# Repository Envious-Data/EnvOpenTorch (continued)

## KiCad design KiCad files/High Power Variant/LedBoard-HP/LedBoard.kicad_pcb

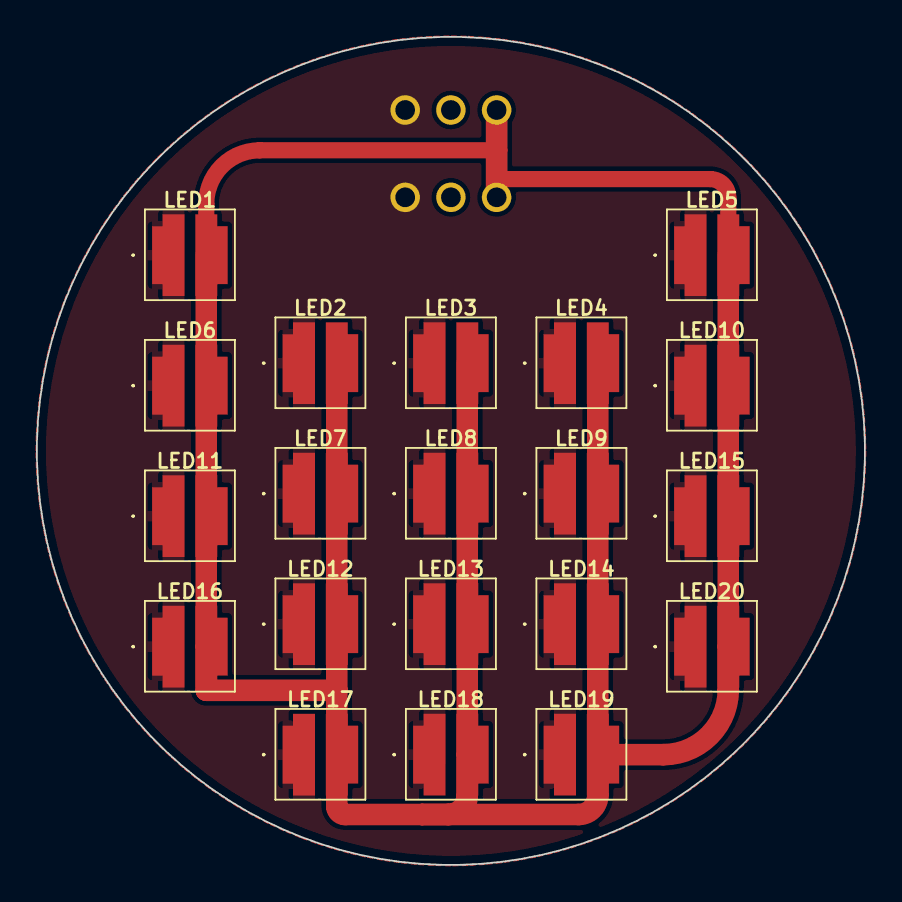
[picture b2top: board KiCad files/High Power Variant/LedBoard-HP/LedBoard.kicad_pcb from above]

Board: 2 copper layers, 46.0 x 46.0 mm, 21 parts (1 on the bottom side), 2 nets.

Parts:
J4: 7-5530843-7; 755308437
LED1, LED2, LED3, LED4, LED5, LED6, LED7, LED8, LED9, LED10, LED11, LED12, LED13, LED14, LED15, LED16, LED17, LED18, LED19, LED20: L1505790500600000

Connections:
GND: J4.5, J4.6, LED1.1 (K_1), LED1.3 (K_2), LED2.1 (K_1), LED2.3 (K_2), LED3.1 (K_1), LED3.3 (K_2), LED4.1 (K_1), LED4.3 (K_2), LED5.1 (K_1), LED5.3 (K_2), LED6.1 (K_1), LED6.3 (K_2), LED7.1 (K_1), LED7.3 (K_2), LED8.1 (K_1), LED8.3 (K_2), LED9.1 (K_1), LED9.3 (K_2), LED10.1 (K_1), LED10.3 (K_2), LED11.1 (K_1), LED11.3 (K_2), LED12.1 (K_1), LED12.3 (K_2), LED13.1 (K_1), LED13.3 (K_2), LED14.1 (K_1), LED14.3 (K_2), LED15.1 (K_1), LED15.3 (K_2), LED16.1 (K_1), LED16.3 (K_2), LED17.1 (K_1), LED17.3 (K_2), LED18.1 (K_1), LED18.3 (K_2), LED19.1 (K_1), LED19.3 (K_2), LED20.1 (K_1), LED20.3 (K_2)
VCC: J4.1, J4.2, LED1.2 (A_1), LED1.4 (A_2), LED2.2 (A_1), LED2.4 (A_2), LED3.2 (A_1), LED3.4 (A_2), LED4.2 (A_1), LED4.4 (A_2), LED5.2 (A_1), LED5.4 (A_2), LED6.2 (A_1), LED6.4 (A_2), LED7.2 (A_1), LED7.4 (A_2), LED8.2 (A_1), LED8.4 (A_2), LED9.2 (A_1), LED9.4 (A_2), LED10.2 (A_1), LED10.4 (A_2), LED11.2 (A_1), LED11.4 (A_2), LED12.2 (A_1), LED12.4 (A_2), LED13.2 (A_1), LED13.4 (A_2), LED14.2 (A_1), LED14.4 (A_2), LED15.2 (A_1), LED15.4 (A_2), LED16.2 (A_1), LED16.4 (A_2), LED17.2 (A_1), LED17.4 (A_2), LED18.2 (A_1), LED18.4 (A_2), LED19.2 (A_1), LED19.4 (A_2), LED20.2 (A_1), LED20.4 (A_2)

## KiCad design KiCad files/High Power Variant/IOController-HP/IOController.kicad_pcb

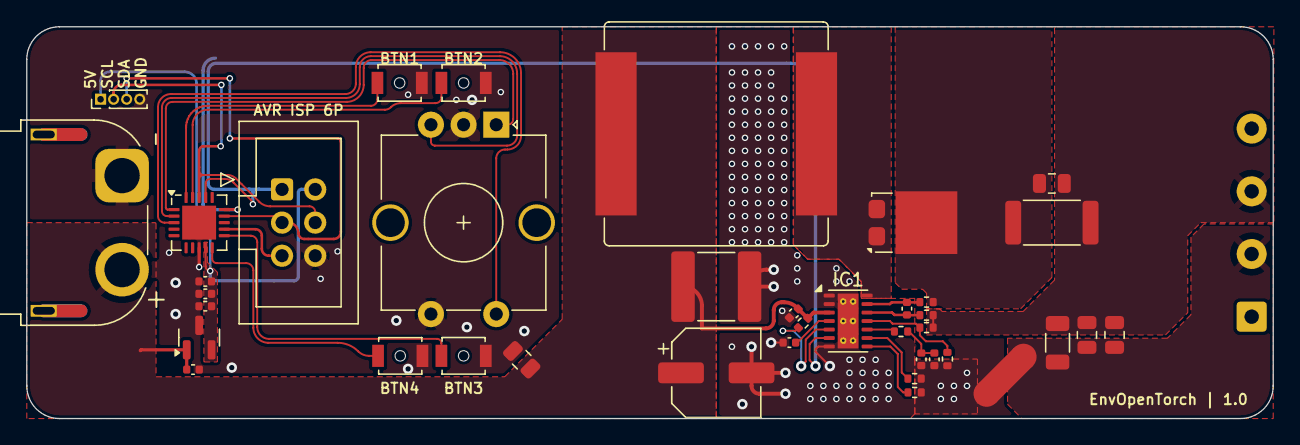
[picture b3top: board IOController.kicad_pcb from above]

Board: 2 copper layers, 95.4 x 30.0 mm, 40 parts (0 on the bottom side), 27 nets.

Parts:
C1: 0401 1uF 35V; C_0402_1005Metric
C2: 0401 2.2uF 6.3V; C_0402_1005Metric
C3: 0401 1uF 6.3V; C_0402_1005Metric
C4: 0401 10uF 6.3V; C_0402_1005Metric
C5: 50V 0.1uF 0805; C_0805_2012Metric
C7: 50V 68uF; CP_Elec_6.3x3
C8: 50V 22uF 2220; C_2220_5750Metric
C12, C13: 25V 1uF 0402; C_0402_1005Metric
C14: 16V 0.1uF 0402; C_0402_1005Metric
C15, C16: 10V 10nF 0402; C_0402_1005Metric
C17: Csense 50V 30uF 0805; C_0805_2012Metric
C18: 100V 0.1uF 0805; C_0805_2012Metric
C19: 100V 1uF 0805; C_0805_2012Metric
C20: 100V 2.2uF 1205; C_1206_3216Metric
D1: FSV12100V; TO-277A
IC1: TPS923654DMTR; VSON-14-1EP_3x4.45mm_P0.65mm_EP1.6x4.2mm_ThermalVias
J1: AVR-ISP-6; IDC-Header_2x03_P2.54mm_Vertical
J2: XT60 Horizontal Socket; AMASS_XT60PW-F_1x02_P7.20mm_Horizontal
J3: Conn_01x04; PinHeader_1x04_P1.00mm_Vertical
J101: Conn_01x04; SolderWire-0.5sqmm_1x04_P4.8mm_D0.9mm_OD2.3mm
L1: SRP1770TA-220M; L_Bourns_SRP1770TA_16.9x16.9mm
NT1: NetTie; NetTie-2_SMD_Pad2.0mm
R5: 10K 0402; R_0402_1005Metric
R6: Rfset 160K 0402; R_0402_1005Metric
R7: Rtemp 57K6 0402; R_0402_1005Metric
R8: Rcomp 825ohm 0402; R_0402_1005Metric
R9: 2512 33mR; R_2512_6332Metric
R10: Rovp1 500K 0402; R_0402_1005Metric
R11: Rovp2 10K 0402; R_0402_1005Metric
R12, R13: 0Ω 0402; R_0402_1005Metric
SW1: EC12; RotaryEncoder_Alps_EC12E-Switch_Vertical_H20mm_CircularMoun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
SW101, SW102, SW103, SW104: B3U; SW_SPST_B3U-1000P-B
U1: AP7384-50SA; SOT-23
U2: ATtiny1634-M; QFN-20-1EP_4x4mm_P0.5mm_EP2.6x2.6mm

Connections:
+5V: C2.1, C3.1, C4.1, J1.2 (VCC), J3.1, U1.2 (VO), U2.9 (VCC)
/LED Driver/CSN: C14.2, IC1.13 (CSN), R12.1
/LED Driver/CSP: C14.1, IC1.12 (CSP), R13.1
/MCU/PC3: J1.5 (~RST), U2.12 (~RESET/PC3)
BTN1: SW101.1, U2.20 (PA7)
BTN2: SW102.1, U2.19 (PB0)
BTN3: SW103.1, U2.11 (XTAL2/PC4)
BTN4: SW104.1, U2.10 (XTAL1/PC5)
BTN5: SW1.S1, U2.3 (PA4)
GND: C1.2, C2.2, C3.2, C4.2, C5.2, C7.2, C8.2, C12.2, C13.1, C15.2, C16.2, IC1.1 (PGND), IC1.2 (AGND), IC1.7 (FAULT), IC1.15 (EP), J1.6 (GND), J2.1, J3.4, NT1.1, R6.2, R7.2, R11.1, SW1.C, SW1.S2, SW101.2, SW102.2, SW103.2, SW104.2, U1.3 (GND), U2.8 (GND), U2.21 (GND)
LED V+: C17.2, C18.1, C19.1, C20.1, J101.3, R9.2, R10.2, R13.2
LED_PWM_5V: IC1.6 (EN/PWM), J1.1 (MISO), U2.17 (PB2)
LED_V-: C18.2, C19.2, C20.2, J101.2, NT1.2
unnamed: C15.1, C16.1, R8.2
unnamed: C17.1, D1.3 (K), R9.1, R12.2
unnamed: IC1.5 (ADIM/HD), R5.2
unnamed: IC1.10 (COMP), R8.1
unnamed: IC1.9 (FSET), R6.1
unnamed: D1.1 (A), D1.2 (A), IC1.14 (SW), L1.2
unnamed: IC1.8 (TEMP), R7.1
unnamed: IC1.11 (UVP), R10.1, R11.2
unnamed: C13.2, IC1.4 (VCC)
ROT_A: SW1.A, U2.1 (PA6)
ROT_B: SW1.B, U2.2 (PA5)
SCL: J1.3 (SCK), J3.3, U2.14 (PC1)
SDA: J1.4 (MOSI), J3.2, U2.18 (PB1)
VCC: C1.1, C5.1, C7.1, C8.1, C12.1, IC1.3 (VIN), J2.2, L1.1, R5.1, U1.1 (VI)

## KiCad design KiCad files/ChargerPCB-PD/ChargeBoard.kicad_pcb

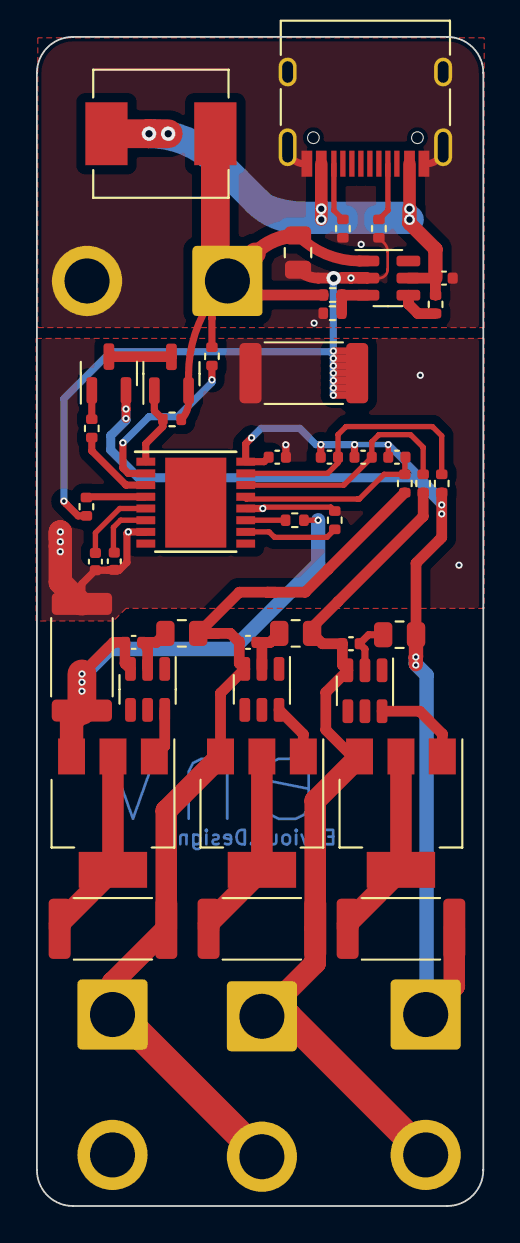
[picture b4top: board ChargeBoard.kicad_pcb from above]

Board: 2 copper layers, 24.8 x 65.0 mm, 49 parts (0 on the bottom side), 34 nets.

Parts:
BAT1, BAT2, BAT3: Conn_01x02; SolderWire-2sqmm_1x02_P7.8mm_D2mm_OD3.9mm
C1, C2, C3, C6, C7, C8, C9, C10: 0.1uF 0402; C_0402_1005Metric
C4: 22uF 0402; C_0402_1005Metric
C5: 22uF 0805 25V; C_0805_2012Metric
C11: 2.2uF 0402; C_0402_1005Metric
J1: USB_C_Receptacle_USB2.0; USB_C_Receptacle_HRO_TYPE-C-31-M-12
J101: Conn_01x02; SolderWire-2sqmm_1x02_P7.8mm_D2mm_OD3.9mm
L1: 22uH 10A; L_Sunlord_MWSA0605S
Q1, Q2, Q3: BSP89; SOT-223-3_TabPin2
Q4, Q5: AO3401A; SOT-23
R1, R4, R6: 47 2512; R_2512_6332Metric
R2, R3, R5: 100 0805; R_0805_2012Metric
R7: 10K 0402; R_0402_1005Metric
R8, R9, R21, R22: 5.1K 0402; R_0402_1005Metric
R10: 62K 0402; R_0402_1005Metric
R11: 3K 0402; R_0402_1005Metric
R18, R19, R20, R25, R26, R27: 1K 0402; R_0402_1005Metric
R23: 1M 0402; R_0402_1005Metric
R24: 0r 2512; R_2512_6332Metric
R103: 51r 2512; R_2512_6332Metric
U1, U2, U3: HY2213; SOT-23-6
U4: MT3608; SOT-23-6
U9: 8254; HTSSOP-16-1EP_4.4x5mm_P0.65mm_EP3.4x5mm

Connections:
+12V: C5.1, J101.1, L1.2, Q4.2 (S), R10.1, R22.2, R23.2, U4.1 (SW)
/VDD: BAT3.1, C6.1, C7.1, C8.1, C11.1, Q5.2 (S), R5.1, R6.1, R27.2, U9.16 (VDD)
/VSS: C9.2, C10.2, C11.2, R18.2, R24.2, R103.2, U9.7 (VSS), U9.12 (VCC4)
GND: C4.2, C5.2, J1.A1 (GND), J1.A12 (GND), J1.B1 (GND), J1.B12 (GND), J1.S1 (SHIELD), J101.2, R8.1, R9.1, R11.2, R20.1, R24.1, U4.2 (GND)
unnamed: BAT1.1, BAT2.2, C2.2, Q2.3 (S), R1.1, R2.1, R25.2, U2.3 (VSS)
unnamed: BAT1.2, C1.2, Q1.3 (S), R19.2, R103.1, U1.3 (VSS)
unnamed: BAT2.1, BAT3.2, C3.2, Q3.3 (S), R3.1, R4.1, R26.2, U3.3 (VSS)
unnamed: J1.A5 (CC1), R8.2
unnamed: J1.B5 (CC2), R9.2
unnamed: Q1.2 (D), R1.2
unnamed: Q1.1 (G), U1.6 (Out)
unnamed: Q2.2 (D), R4.2
unnamed: Q2.1 (G), U2.6 (Out)
unnamed: Q3.2 (D), R6.2
unnamed: Q3.1 (G), U3.6 (Out)
unnamed: Q4.3 (D), Q5.3 (D)
unnamed: Q4.1 (G), R23.1, U9.1 (COP)
unnamed: Q5.1 (G), R21.2
unnamed: C1.1, R2.2, U1.2 (VDD)
unnamed: C2.1, R3.2, U2.2 (VDD)
unnamed: C3.1, R5.2, U3.2 (VDD)
unnamed: R7.1, U4.4 (EN)
unnamed: R10.2, R11.1, U4.3 (FB)
unnamed: C9.1, U9.6 (CCT)
unnamed: C10.1, U9.5 (CDT)
unnamed: R19.1, U9.11 (CTL)
unnamed: R21.1, U9.3 (DOP)
unnamed: R18.1, U9.10 (SEL)
unnamed: C6.2, R27.1, U9.15 (VCC1)
unnamed: C7.2, R26.1, U9.14 (VCC2)
unnamed: C8.2, R25.1, U9.13 (VCC3)
unnamed: R20.2, U9.4 (VINI)
unnamed: R22.1, U9.2 (VMP)
VBUS: C4.1, J1.A4 (VBUS), J1.A9 (VBUS), J1.B4 (VBUS), J1.B9 (VBUS), L1.1, R7.2, U4.5 (IN)

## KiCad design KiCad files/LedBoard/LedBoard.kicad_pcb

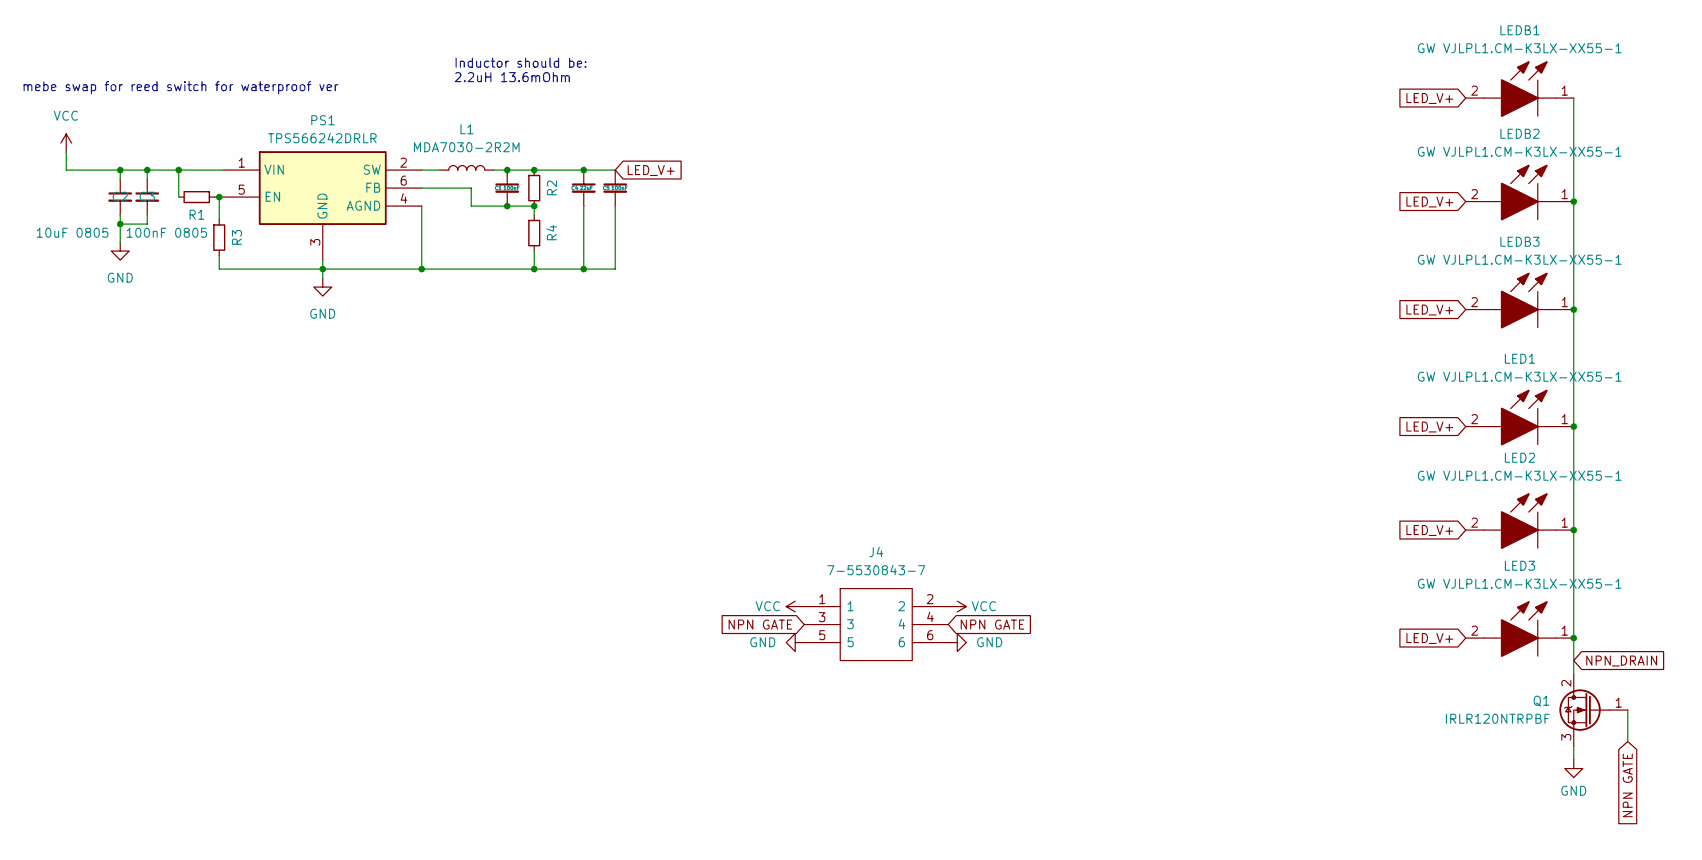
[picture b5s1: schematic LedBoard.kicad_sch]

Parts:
C1, C5: 100nF; C_0805_2012Metric
C2: 10uF 0805; C_0805_2012Metric
C3: 100nF 0805; C_0805_2012Metric
C4: 22uF; C_0805_2012Metric
J4: 7-5530843-7; 755308437; Mouser Part Number 571-7-5530843-7
L1: MDA7030-2R2M; L_Coilcraft_XAL7030-222
LED1, LED2, LED3: GW VJLPL1.CM-K3LX-XX55-1; GW_VJLPE1.CM_0.91x0.91mm; Manufacturer_Part_Number GW VJLPL1.CM-K3LX-XX51-1
LEDB1, LEDB2, LEDB3: GW VJLPL1.CM-K3LX-XX55-1; GWVJLPL1CMK3LXXX511; Manufacturer_Part_Number GW VJLPL1.CM-K3LX-XX51-1
PS1: TPS566242DRLR; SOT-563; Mouser Part Number 595-TPS566242DRLR
Q1: IRLR120NTRPBF; TO-252-2
R1: 100K 0805; R_0805_2012Metric
R2: 120K 0805; R_0805_2012Metric
R3: 23.2K 0805; R_0805_2012Metric
R4: 30K 0805; R_0805_2012Metric

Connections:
GND: C2.2, C3.2, C4.2, C5.2, J4.5, J4.6, PS1.3 (GND), PS1.4 (AGND), Q1.3 (S), R3.2, R4.2
LED_V+: C1.1, C4.1, C5.1, L1.2, LED1.2, LED2.2, LED3.2, LEDB1.2, LEDB2.2, LEDB3.2, R2.1
NPN GATE: J4.3, J4.4, Q1.1 (G)
NPN_DRAIN: LED1.1, LED2.1, LED3.1, LEDB1.1, LEDB2.1, LEDB3.1, Q1.2 (D)
unnamed: PS1.5 (EN), R1.1, R3.1
unnamed: C1.2, PS1.6 (FB), R2.2, R4.1
unnamed: L1.1, PS1.2 (SW)
VCC: C2.1, C3.1, J4.1, J4.2, PS1.1 (VIN), R1.2

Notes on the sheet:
Inductor should be: 2.2uH 13.6mOhm
mebe swap for reed switch for waterproof ver

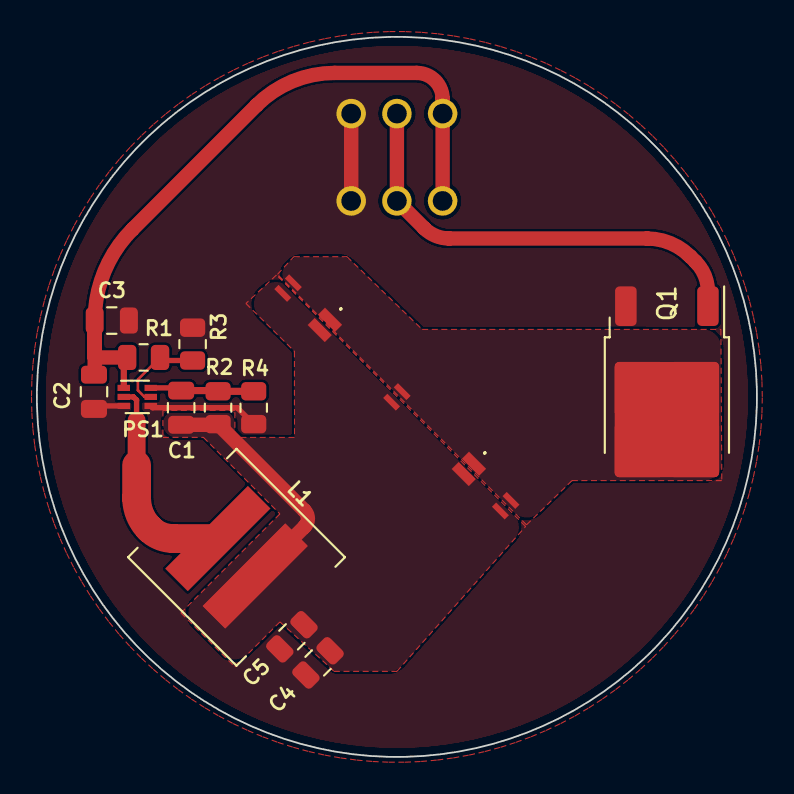
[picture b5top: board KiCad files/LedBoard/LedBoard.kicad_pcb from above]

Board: 2 copper layers, 40.0 x 40.0 mm, 18 parts (1 on the bottom side), 8 nets.

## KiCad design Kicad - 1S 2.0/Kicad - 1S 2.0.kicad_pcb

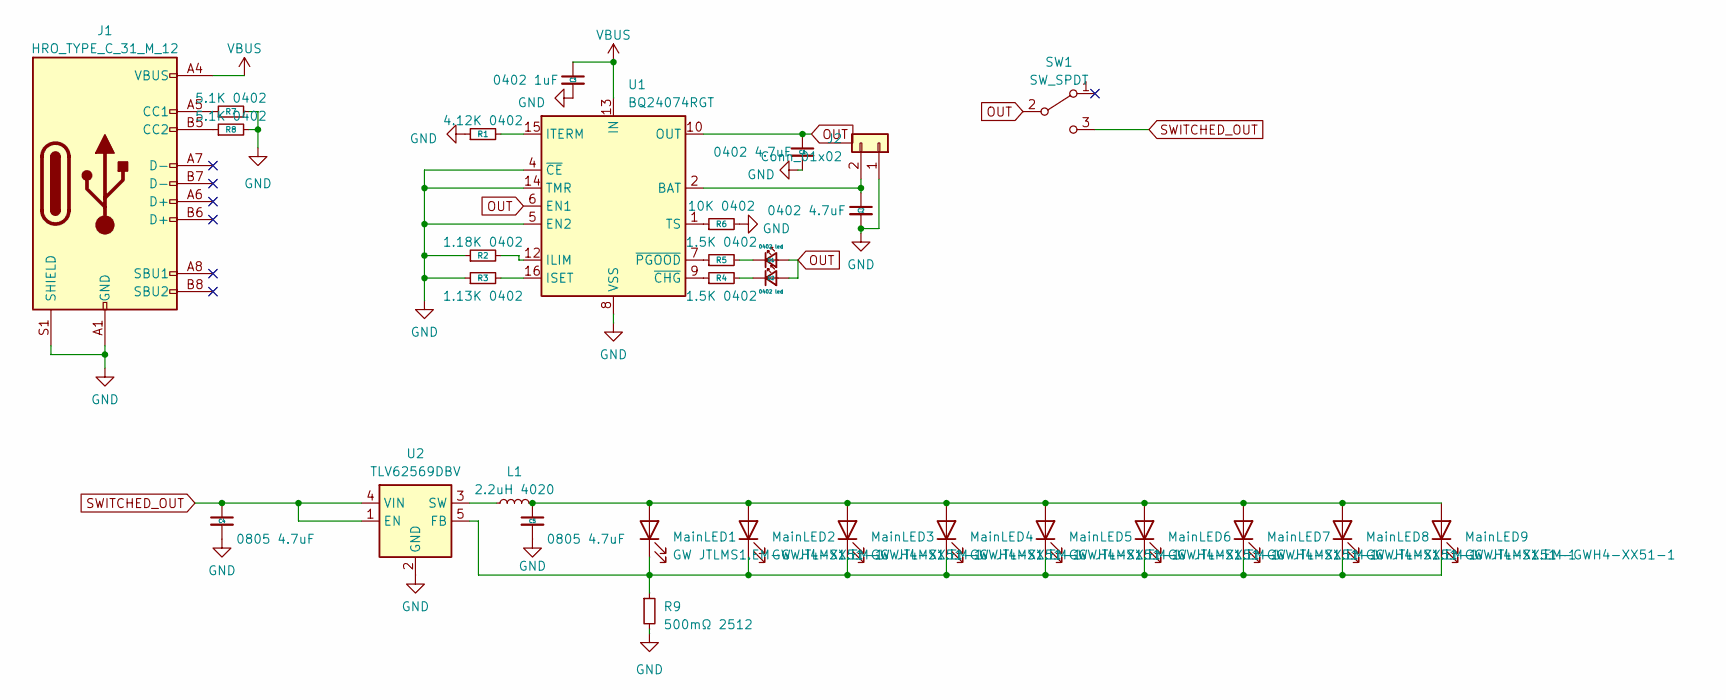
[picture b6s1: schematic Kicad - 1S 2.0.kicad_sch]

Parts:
C1, C2: 0402 4.7uF; C_0402_1005Metric
C3: 0402 1uF; C_0402_1005Metric
C4, C5: 0805 4.7uF; C_0805_2012Metric
D1, D2: 0402 led; LED_0402_1005Metric
J1: HRO_TYPE_C_31_M_12; USB_C_Receptacle_HRO_TYPE-C-31-M-12
J2: Conn_01x02; JST_PH_B2B-PH-K_1x02_P2.00mm_Vertical
L1: 2.2uH 4020; L_Wurth_WE-LQSH-4020
MainLED1, MainLED2, MainLED3, MainLED4, MainLED5, MainLED6, MainLED7, MainLED8, MainLED9: GW JTLMS1.EM-GWH4-XX51-1; LED_PLCC_2835
R1: 4.12K 0402; R_0402_1005Metric
R2: 1.18K 0402; R_0402_1005Metric
R3: 1.13K 0402; R_0402_1005Metric
R4, R5: 1.5K 0402; R_0402_1005Metric
R6: 10K 0402; R_0402_1005Metric
R7, R8: 5.1K 0402; R_0402_1005Metric
R9: 500mΩ 2512; R_2512_6332Metric
SW1: SW_SPDT; SW_SPDT_PCM12
U1: BQ24074RGT; VQFN-16-1EP_3x3mm_P0.5mm_EP1.6x1.6mm
U2: TLV62569DBV; SOT-23-5

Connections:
GND: C1.2, C2.2, C3.2, C4.2, C5.2, J1.A1 (GND), J1.A12 (GND), J1.B1 (GND), J1.B12 (GND), J1.S1 (SHIELD), J2.1, R1.1, R2.1, R3.1, R6.2, R7.2, R8.2, R9.2, U1.4 (~CE), U1.5 (EN2), U1.8 (VSS), U1.14 (TMR), U1.17 (VSS), U2.2 (GND)
unnamed: D1.1 (K), R5.2
unnamed: D2.1 (K), R4.2
unnamed: J1.A5 (CC1), R7.1
unnamed: J1.B5 (CC2), R8.1
unnamed: C2.1, J2.2, U1.2 (BAT), U1.3 (BAT)
unnamed: C5.1, L1.2, MainLED1.2 (A), MainLED2.2 (A), MainLED3.2 (A), MainLED4.2 (A), MainLED5.2 (A), MainLED6.2 (A), MainLED7.2 (A), MainLED8.2 (A), MainLED9.2 (A)
unnamed: MainLED1.1 (K), MainLED2.1 (K), MainLED3.1 (K), MainLED4.1 (K), MainLED5.1 (K), MainLED6.1 (K), MainLED7.1 (K), MainLED8.1 (K), MainLED9.1 (K), R9.1, U2.5 (FB)
unnamed: R2.2, U1.12 (ILIM)
unnamed: R3.2, U1.16 (ISET)
unnamed: R1.2, U1.15 (ITERM)
unnamed: R6.1, U1.1 (TS)
unnamed: R4.1, U1.9 (~CHG)
unnamed: R5.1, U1.7 (~PGOOD)
unnamed: L1.1, U2.3 (SW)
OUT: C1.1, D1.2 (A), D2.2 (A), SW1.2 (B), U1.6 (EN1), U1.10 (OUT), U1.11 (OUT)
SWITCHED_OUT: C4.1, SW1.3 (C), U2.1 (EN), U2.4 (VIN)
VBUS: C3.1, J1.A4 (VBUS), J1.A9 (VBUS), J1.B4 (VBUS), J1.B9 (VBUS), U1.13 (IN)

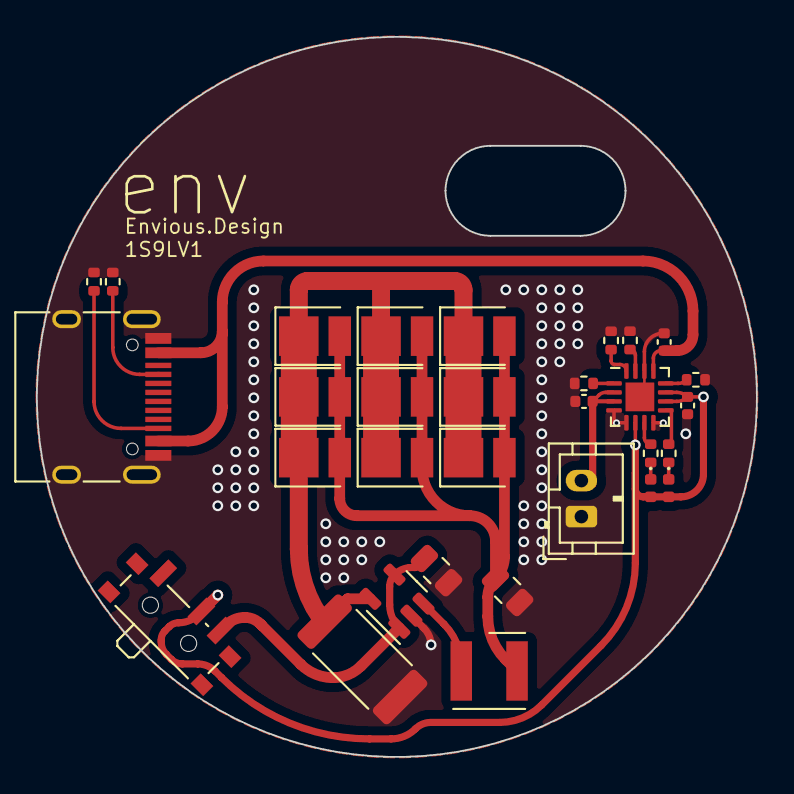
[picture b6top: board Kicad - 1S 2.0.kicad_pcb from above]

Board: 2 copper layers, 40.0 x 40.0 mm, 31 parts (0 on the bottom side), 18 nets.

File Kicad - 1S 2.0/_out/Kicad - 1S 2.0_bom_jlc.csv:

"Comment","Designator","Footprint","LCSC Part #"
"0402 4.7uF","C1,C2","C_0402_1005Metric","no_part_number"
"0402 1uF","C3","C_0402_1005Metric","no_part_number"
"0805 4.7uF","C4,C5","C_0805_2012Metric","no_part_number"
"0402 led","D1,D2","LED_0402_1005Metric","no_part_number"
"HRO_TYPE_C_31_M_12","J1","USB_C_Receptacle_HRO_TYPE-C-31-M-12","no_part_number"
"Conn_01x02","J2","JST_PH_B2B-PH-K_1x02_P2.00mm_Vertical","no_part_number"
"2.2uH 4020","L1","L_Wurth_WE-LQSH-4020","no_part_number"
"GW JTLMS1.EM-GWH4-XX51-1","MAINLED1,MAINLED2,MAINLED3,MAINLED4,MAINLED5,MAINLED6,MAINLED7,MAINLED8,MAINLED9","LED_PLCC_2835","no_part_number"
"4.12K 0402","R1","R_0402_1005Metric","no_part_number"
"1.18K 0402","R2","R_0402_1005Metric","no_part_number"
"1.13K 0402","R3","R_0402_1005Metric","no_part_number"
"1.5K 0402","R4,R5","R_0402_1005Metric","no_part_number"
"10K 0402","R6","R_0402_1005Metric","no_part_number"
"5.1K 0402","R7,R8","R_0402_1005Metric","no_part_number"
"500mΩ 2512","R9","R_2512_6332Metric","no_part_number"
"SW_SPDT","SW1","SW_SPDT_PCM12","no_part_number"
"BQ24074RGT","U1","VQFN-16-1EP_3x3mm_P0.5mm_EP1.6x1.6mm","no_part_number"
"TLV62569DBV","U2","SOT-23-5","no_part_number"

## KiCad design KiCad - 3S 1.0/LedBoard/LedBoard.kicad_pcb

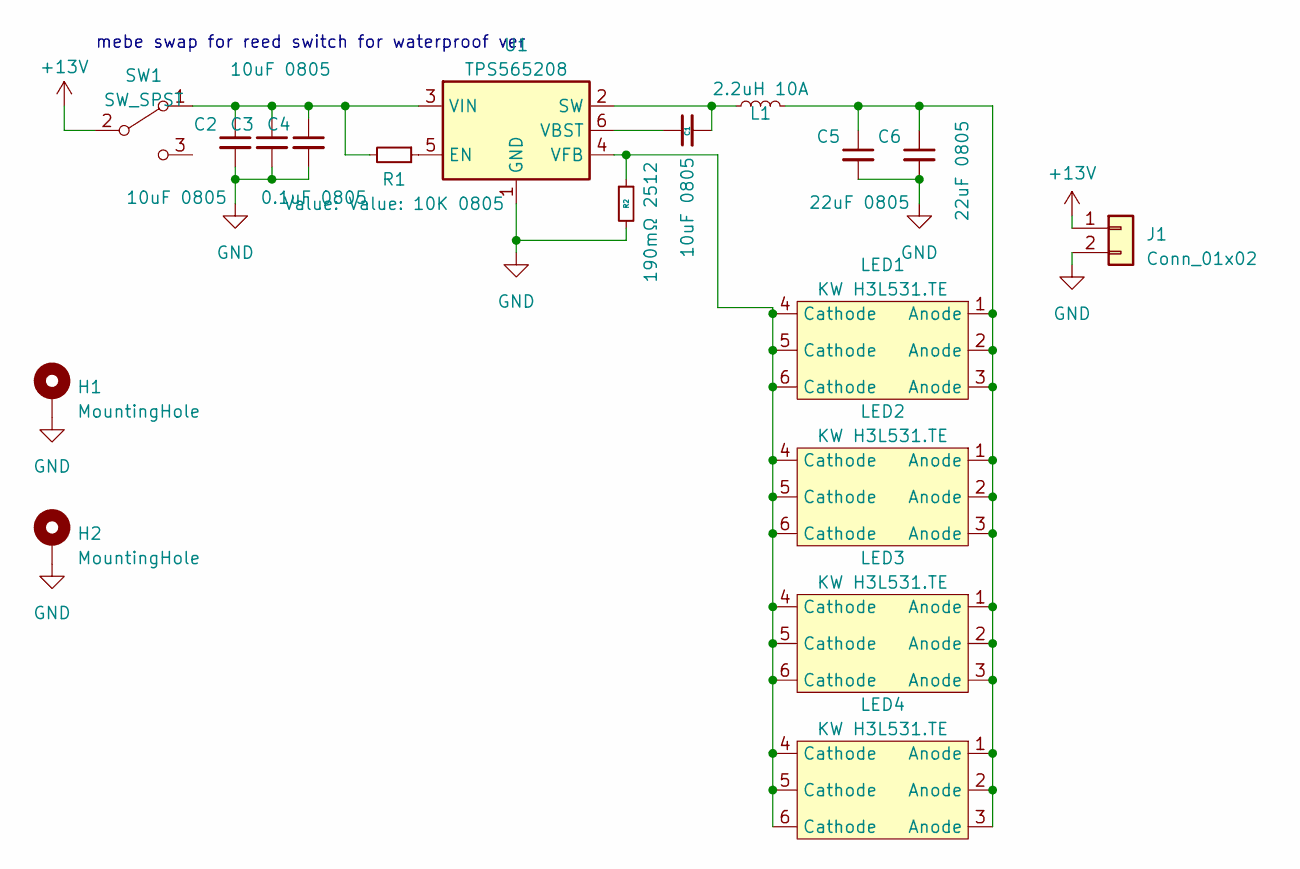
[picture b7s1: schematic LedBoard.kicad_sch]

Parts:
C1, C2, C3: 10uF 0805; C_0805_2012Metric
C4: 0.1uF 0805; C_0805_2012Metric
C5, C6: 22uF 0805; C_0805_2012Metric
H1, H2: MountingHole; MountingHole_2.2mm_M2_DIN965_Pad
J1: Conn_01x02; SolderWire-2sqmm_1x02_P7.8mm_D2mm_OD3.9mm
L1: 2.2uH 10A; L_Sunlord_MWSA0624S
LED1, LED2, LED3, LED4: KW H3L531.TE; KW_H3L531.TE
R1: Value: 10K 0805; R_0805_2012Metric
R2: 190mΩ 2512; R_2512_6332Metric
SW1: SW_SPST; SolderWire-0.1sqmm_1x03_P3.6mm_D0.4mm_OD1mm
U1: TPS565208; SOT-23-6

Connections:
+12V: J1.1, SW1.2 (B)
GND: C2.2, C3.2, C4.2, C5.2, C6.2, H1.1, H2.1, J1.2, R2.2, U1.1 (GND)
unnamed: C5.1, C6.1, L1.2, LED1.1 (Anode), LED1.2 (Anode), LED1.3 (Anode), LED2.1 (Anode), LED2.2 (Anode), LED2.3 (Anode), LED3.1 (Anode), LED3.2 (Anode), LED3.3 (Anode), LED4.1 (Anode), LED4.2 (Anode), LED4.3 (Anode)
unnamed: C2.1, C3.1, C4.1, R1.2, SW1.1 (A), U1.3 (VIN)
unnamed: R1.1, U1.5 (EN)
unnamed: C1.2, L1.1, U1.2 (SW)
unnamed: C1.1, U1.6 (VBST)
unnamed: LED1.4 (Cathode), LED1.5 (Cathode), LED1.6 (Cathode), LED2.4 (Cathode), LED2.5 (Cathode), LED2.6 (Cathode), LED3.4 (Cathode), LED3.5 (Cathode), LED3.6 (Cathode), LED4.4 (Cathode), LED4.5 (Cathode), LED4.6 (Cathode), R2.1, U1.4 (VFB)

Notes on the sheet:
mebe swap for reed switch for waterproof ver

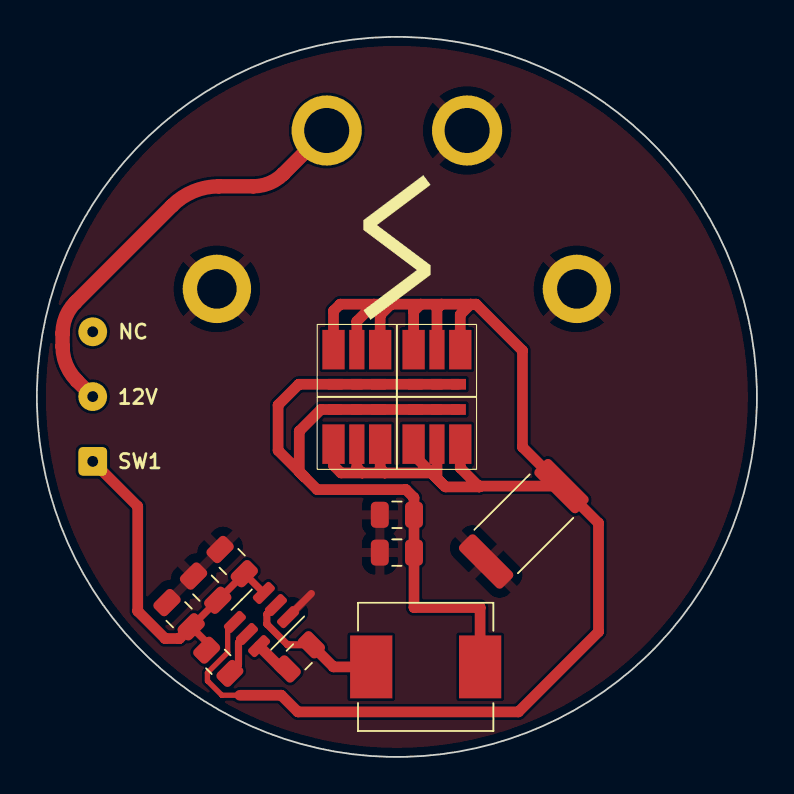
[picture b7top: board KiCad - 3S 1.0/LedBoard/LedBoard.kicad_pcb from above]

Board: 2 copper layers, 40.0 x 40.0 mm, 18 parts (0 on the bottom side), 8 nets.

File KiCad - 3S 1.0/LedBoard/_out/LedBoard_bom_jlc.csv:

"Comment","Designator","Footprint","LCSC Part #"
"10uF 0805","C1,C2,C3","C_0805_2012Metric","no_part_number"
"0.1uF 0805","C4","C_0805_2012Metric","no_part_number"
"22uF 0805","C5,C6","C_0805_2012Metric","no_part_number"
"MountingHole","H1,H2","MountingHole_2.2mm_M2_DIN965_Pad","no_part_number"
"Conn_01x02","J1","SolderWire-2sqmm_1x02_P7.8mm_D2mm_OD3.9mm","no_part_number"
"2.2uH 10A","L1","L_Sunlord_MWSA0624S","no_part_number"
"KW H3L531.TE","LED1,LED2,LED3,LED4","KW_H3L531.TE","no_part_number"
"Value: Value: 10K 0805","R1","R_0805_2012Metric","no_part_number"
"190mΩ 2512","R2","R_2512_6332Metric","no_part_number"
"SW_SPST","SW1","SW_SPDT_PCM12","no_part_number"
"TPS565208","U1","SOT-23-6","no_part_number"

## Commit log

2023-02-20 Initial commit +1
2023-02-20 uploaded missing file
2023-03-12 created lower cost single cell variant with less leds, this version will draw 1.2A possibly more due to losses and what not but can charge at 1.5A
2023-03-12 changed LEDs over to a standard format to make the board cheaper
2023-03-13 small fix to gitignore to allow gerber CSVs
2023-03-19 broke up 3SV1 into two separate boards (unfinished work)
2023-03-20 Finished up LED PCB and made some small tweaks and fixes to main board.
2023-04-01 swapped around some parts and re-routed various bits and generated gerbers
2023-08-24 swapped the switch for pin headers so a switch can be wired externally to the PCB.
2023-09-18 started work on adding USB PD 100W support.
2023-09-18 drew up the schematic to match the reference design from TI for 100W PD charger
2023-09-19 added TVS2200 to schematic matching the reference design.
2023-09-19 updated all symbols to match BOM
2023-09-19 updated inductors.
2023-09-19 C35 had wrong footprint, changed from 0603 to 0402
2023-09-21 few small corrections i forgot to commit
2023-12-31 Added a note in schematic, Current version is capable of 45W and isnt advised for 65W or more, I should change the IC out.
2024-02-03 Added new footprint for smaller cheaper, newer led.
2024-03-01 renamed main project folder as this is going to be a single torch instead of two
2024-03-01 cleanup of parts no longer intend to use.
2024-03-01 swapped regulator, needs leds implemented, osram pure 1414
2024-03-01 added npn mosfet for led pwm controll
2024-03-03 added basic io controller PCB
2024-03-03 swapped regulator for 1.8V instead of 5V for lower power
2024-03-03 Added library for LED
2024-03-03 updated LED board
2024-03-03 added giant npn mosfet on led board, needs to be removed from controller board
2024-03-10 made some small tweaks
2024-03-10 added some parts to controller board for now.
2024-04-04 modified IO board and LED board so they connect together using XT60
2024-04-04 replaced traces with zones
2024-04-04 corrected VCC and GND being swapped
2024-04-04 changed an XT60 to edge connector because I didnt like the XT60 and pin header setup.
2024-04-05 added footprints for some discontinued LEDs i have spare of, added level shifter to ensure gate voltage is above threshold
2024-04-29 some partial work towards modifying the design yet again
2024-05-02 changed regulator again
2024-05-25 updated LED board to use new LEDs
2024-05-25 started re-work of led driver circuit on IO board
2024-05-27 completed circuit, could be laid out better
2024-06-03 laid out the circuit better but less space efficient.
2024-06-03 renamed some stuff
2024-06-04 added some notes on which 240W capable ICs to switch to.
2024-07-13 small adjustment to zones and added stitching vias
2024-07-27 updated small changes
2024-09-07 re-organised some files, started work on implementing 100W and 240W EPR versions of the charge board
2024-09-15 swapped RP2040 for attiny1634, still requires more work.
2024-10-24 made some adjustments to improve design reliability.
2024-10-25 modified design to be closer to reference version.
2024-10-25 made a few small fixes.
2024-11-04 corrected a few things to make life a bit easier.
2024-11-21 Started work on a smaller light.
2025-02-04 updated the schematics and completed the battery charge IC circuit
